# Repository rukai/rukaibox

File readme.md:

# Rukaibox

A custom hitbox controller for platform fighters.
The PCB used is the [gram slim PCB](https://gramctrl.com/products/gram-slim-pcb)
I have a fork of the PCB in this repo purely because I wanted to tweak some things for my own usage while remaining compatible with the standard gram slim PCB.

This design might be interesting to you if you want a fully 3D printable enclosure with a built in lid that flips underneath the controller when in use.
But keep in mind that when the lid is open, it exposes the PCB as an aesthetic choice, which comes with a risk of damage to the PCB.

I also personally use my own [rukaibox firmware](https://github.com/rukai/rukaibox_firmware).
But the [stock gram haybox firmware](https://github.com/GRAMCTRL/HayBox-GRAM) also works just fine and supports a wider range of protocols, games and MCUs.

## BOM

* A gram slim PCB
  * I ordered mine from jlcpcb from the designs in this repo
  * But you should probably just buy yours from <https://gramctrl.com/products/gram-slim-pcb>
* All the printed parts from [the onshape designs](https://cad.onshape.com/documents/f6e7916fda654a648d842c67/w/2435c624e0afcf5d47216714/e/d2b4fc9888a125d6f744d329?renderMode=0&uiState=6768f678e653c701cfa65dbe).
  1. Convert each part to an STL by going through the `base`, `lid`, `switch plate`, `switch plate left`, `switch plate right`, `join` and `woshua` tabs at the bottom of the page.
  For each tab, click on the tab and then right click on each part on the pane on the left and select export.
  Set the format to STL and keep the rest as default.
  2. Then slice and print each STL yourself.
* M3 Screws (all with head length 3mm, head width 5.3mm):
  * 6 X [bolt length: 13.5mm](https://www.aliexpress.com/item/32810872544.html)
* 6 X [M3 square nuts 5.45mm x 5.45mm x 1.7mm](https://www.aliexpress.com/item/1005001612157787.html)
* 21 x [kailh choc hotswap sockets](https://www.aliexpress.com/item/1005003575767699.html)
* 21 x [kailh choc V1 switches](https://www.aliexpress.com/item/1005005066585322.html) (I used whites for the start button and reds for every other button)
* 21 x [kailh choc V1 buttons](https://www.aliexpress.com/item/1005006902597750.html)

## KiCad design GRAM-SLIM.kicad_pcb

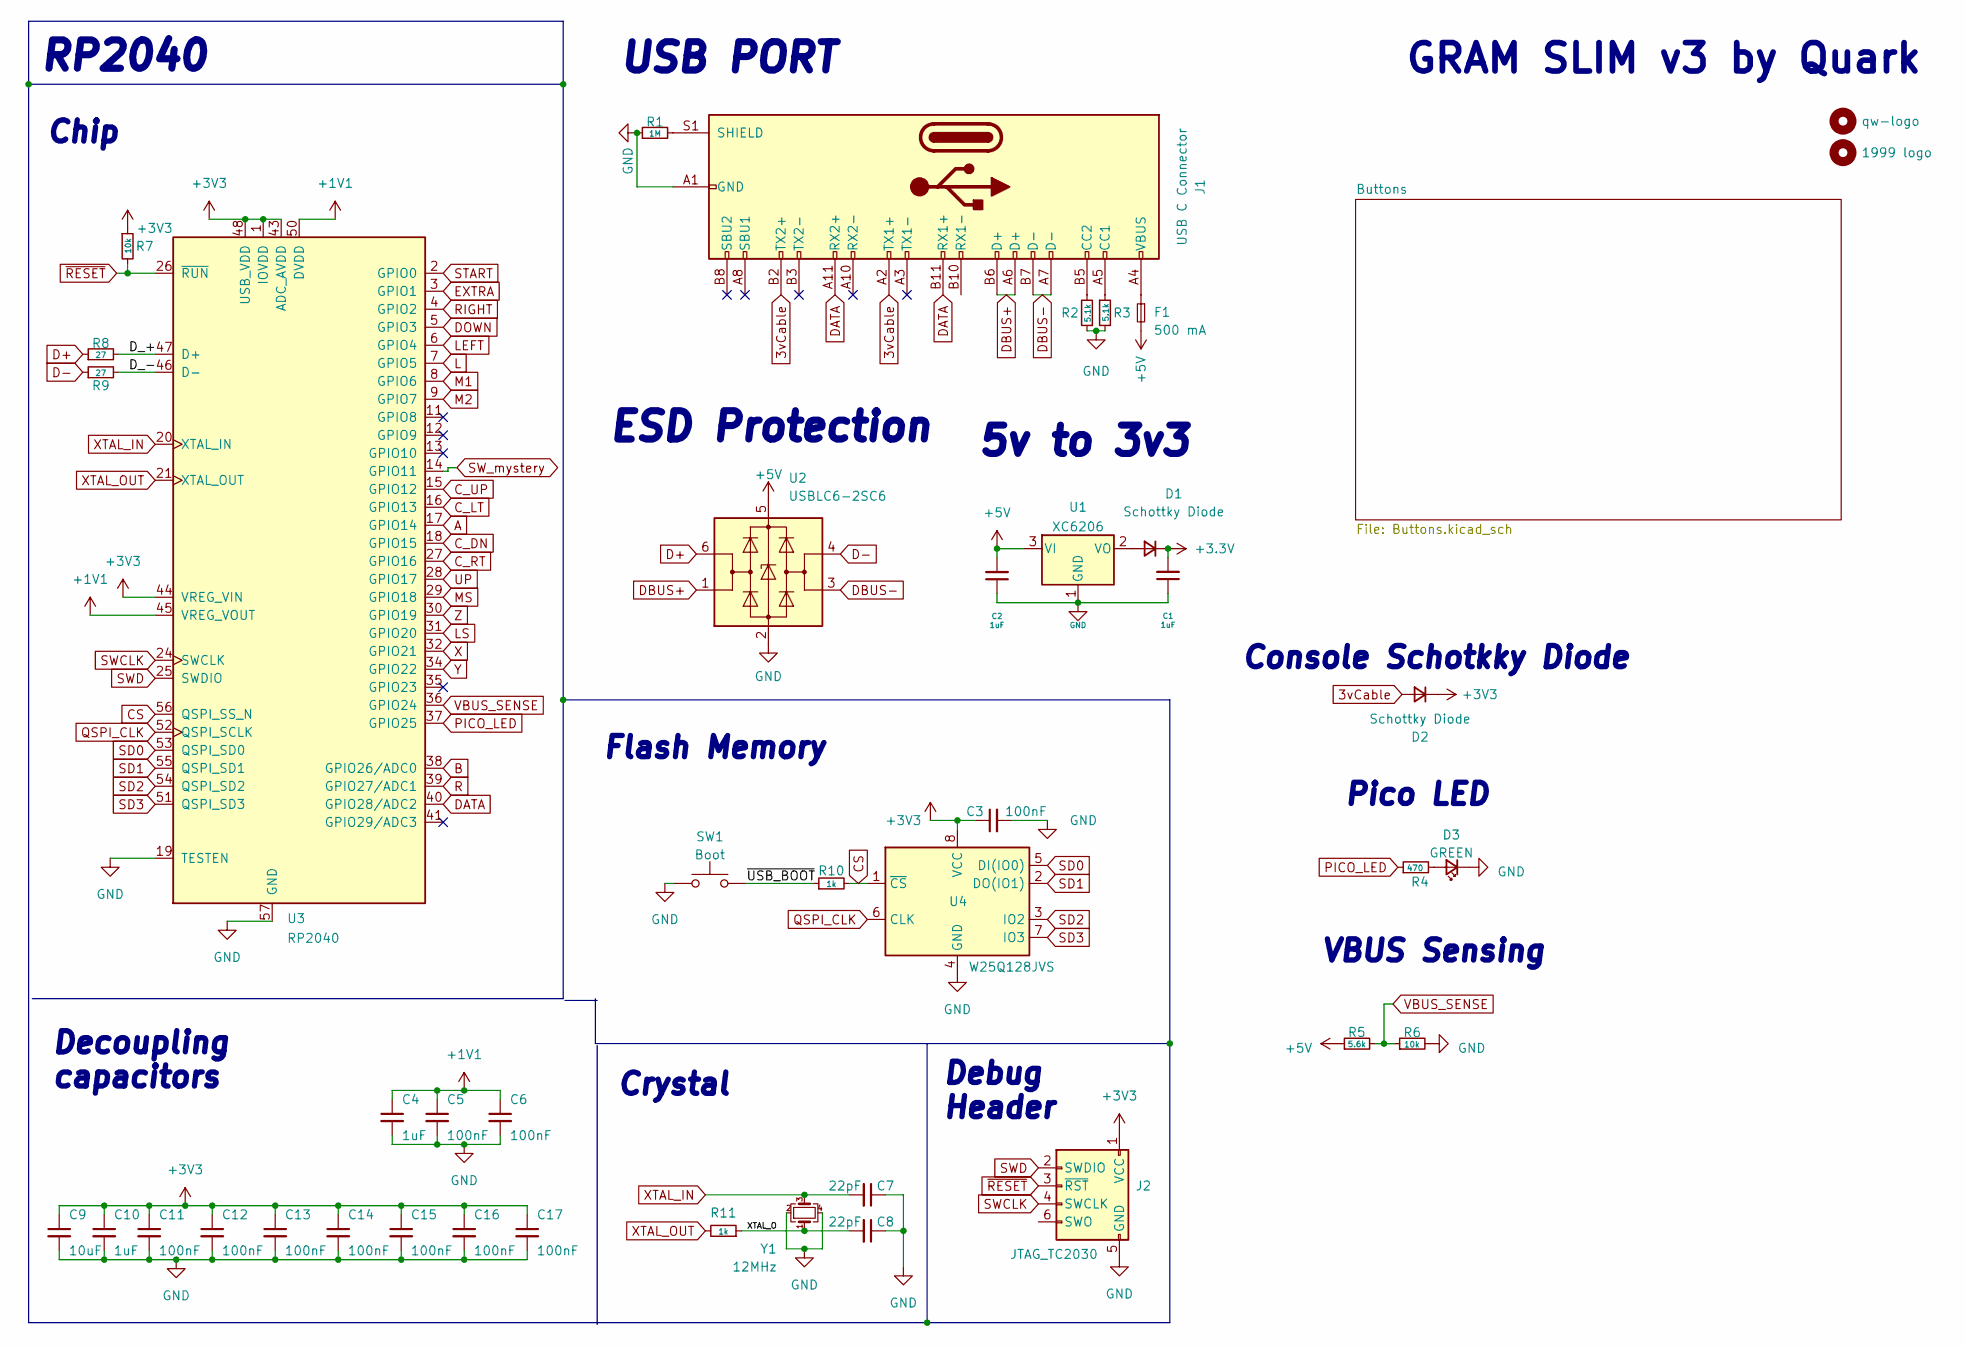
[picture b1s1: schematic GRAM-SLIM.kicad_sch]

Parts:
C1, C2, C4, C10: 1uF; C_0402_1005Metric; LCSC C52923
C3, C5, C6, C11, C12, C13, C14, C15, C16, C17: 100nF; C_0402_1005Metric; LCSC C1525
C7, C8: 22pF; C_0402_1005Metric; LCSC C1555
C9: 10uF; C_0402_1005Metric; LCSC C15525
D1, D2: Schottky Diode; D_SOD-123; LCSC C130880
D3: GREEN; LED_0805_2012Metric
F1: 500 mA; Fuse_1206_3216Metric
H1: qw-logo; qw new logo silk + copper md
H2: 1999 logo; 1999 logo md
J1: USB C Connector; TYPE-C_24P_QCHT; LCSC C456013
J2: JTAG_TC2030; CON_TC2030_outlined
R1: 1M; R_0603_1608Metric; LCSC C25190
R2, R3: 5.1k; R_0402_1005Metric; LCSC C25744
R4: 470; R_0402_1005Metric
R5: 5.6k; R_0603_1608Metric
R6: 10k; R_0603_1608Metric
R7: 10k; R_0402_1005Metric; LCSC C25744
R8, R9: 27; R_0603_1608Metric; LCSC C25190
R10, R11: 1k; R_0402_1005Metric; LCSC C11702
SW1: Boot; SW_SPST_SKQG_WithStem; LCSC C5156480
U1: XC6206; SOT-23; LCSC C5446
U2: USBLC6-2SC6; SOT-23-6
U3: RP2040; RP2040-QFN-56; LCSC C2040
U4: W25Q128JVS; SOIC-8_5.23x5.23mm_P1.27mm; LCSC C97521
Y1: 12MHz; Crystal_SMD_3225-4Pin_3.2x2.5mm; LCSC C9002

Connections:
3vCable: D2.2 (A), J1.A2 (TX1+), J1.B2 (TX2+)
+1V1: C4.1, C5.1, C6.1, U3.23 (DVDD), U3.45 (VREG_VOUT), U3.50 (DVDD)
+5V: C2.2, F1.2, R5.1, U1.3 (VI), U2.5 (VBUS)
/D_+: R8.2, U3.47 (D+)
/D_-: R9.2, U3.46 (D-)
/XTAL_O: C8.2, R11.1, Y1.1
/~USB_BOOT: R10.1, SW1.2
A: U3.17 (GPIO14); also elsewhere on the board
B: U3.38 (GPIO26/ADC0); also elsewhere on the board
CS: R10.2, U3.56 (QSPI_SS_N), U4.1 (~CS)
C_DN: U3.18 (GPIO15); also elsewhere on the board
C_LT: U3.16 (GPIO13); also elsewhere on the board
C_RT: U3.27 (GPIO16); also elsewhere on the board
C_UP: U3.15 (GPIO12); also elsewhere on the board
D+: R8.1, U2.6 (I/O1)
D-: R9.1, U2.4 (I/O2)
DATA: J1.A11 (RX2+), J1.B11 (RX1+), U3.40 (GPIO28/ADC2)
DBUS+: J1.A6 (D+), J1.B6 (D+), U2.1 (I/O1)
DBUS-: J1.A7 (D-), J1.B7 (D-), U2.3 (I/O2)
DOWN: U3.5 (GPIO3); also elsewhere on the board
EXTRA: U3.3 (GPIO1); also elsewhere on the board
GND: C1.1, C2.1, C3.2, C4.2, C5.2, C6.2, C7.1, C8.1, C9.2, C10.2, C11.2, C12.2, C13.2, C14.2, C15.2, C16.2, C17.2, D3.1 (K), J1.A1 (GND), J1.A12 (GND), J1.B1 (GND), J1.B12 (GND), J2.5 (GND), R1.1, R2.1, R3.2, R6.2, SW1.1, U1.1 (GND), U2.2 (GND), U3.19 (TESTEN), U3.57 (GND), U4.4 (GND), Y1.2, Y1.4; also elsewhere on the board
L: U3.7 (GPIO5); also elsewhere on the board
LEFT: U3.6 (GPIO4); also elsewhere on the board
LS: U3.31 (GPIO20); also elsewhere on the board
M1: U3.8 (GPIO6); also elsewhere on the board
M2: U3.9 (GPIO7); also elsewhere on the board
MS: U3.29 (GPIO18); also elsewhere on the board
unnamed: D1.2 (A), U1.2 (VO)
unnamed: D3.2 (A), R4.2
unnamed: F1.1, J1.A4 (VBUS), J1.A9 (VBUS), J1.B4 (VBUS), J1.B9 (VBUS)
unnamed: J1.A5 (CC1), R3.1
unnamed: J1.B5 (CC2), R2.2
unnamed: J1.S1 (SHIELD), R1.2
PICO_LED: R4.1, U3.37 (GPIO25)
QSPI_CLK: U3.52 (QSPI_SCLK), U4.6 (CLK)
R: U3.39 (GPIO27/ADC1); also elsewhere on the board
RIGHT: U3.4 (GPIO2); also elsewhere on the board
SD0: U3.53 (QSPI_SD0), U4.5 (DI(IO0))
SD1: U3.55 (QSPI_SD1), U4.2 (DO(IO1))
SD2: U3.54 (QSPI_SD2), U4.3 (IO2)
SD3: U3.51 (QSPI_SD3), U4.7 (IO3)
START: U3.2 (GPIO0); also elsewhere on the board
SWCLK: J2.4 (SWCLK), U3.24 (SWCLK)
SWD: J2.2 (SWDIO), U3.25 (SWDIO)
SW_mystery: U3.14 (GPIO11); also elsewhere on the board
UP: U3.28 (GPIO17); also elsewhere on the board
VBUS_SENSE: R5.2, R6.1, U3.36 (GPIO24)
X: U3.32 (GPIO21); also elsewhere on the board
XTAL_IN: C7.2, U3.20 (XTAL_IN), Y1.3
XTAL_OUT: R11.2, U3.21 (XTAL_OUT)
Y: U3.34 (GPIO22); also elsewhere on the board
Z: U3.30 (GPIO19); also elsewhere on the board
~RESET: J2.3 (~RST), R7.2, U3.26 (~RUN)

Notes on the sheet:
GRAM SLIM v3 by Quark
Flash Memory
5v to 3v3
Pico LED
Crystal
Chip
Console Schotkky Diode
RP2040
VBUS Sensing
Debug Header
USB PORT
ESD Protection
Decoupling capacitors

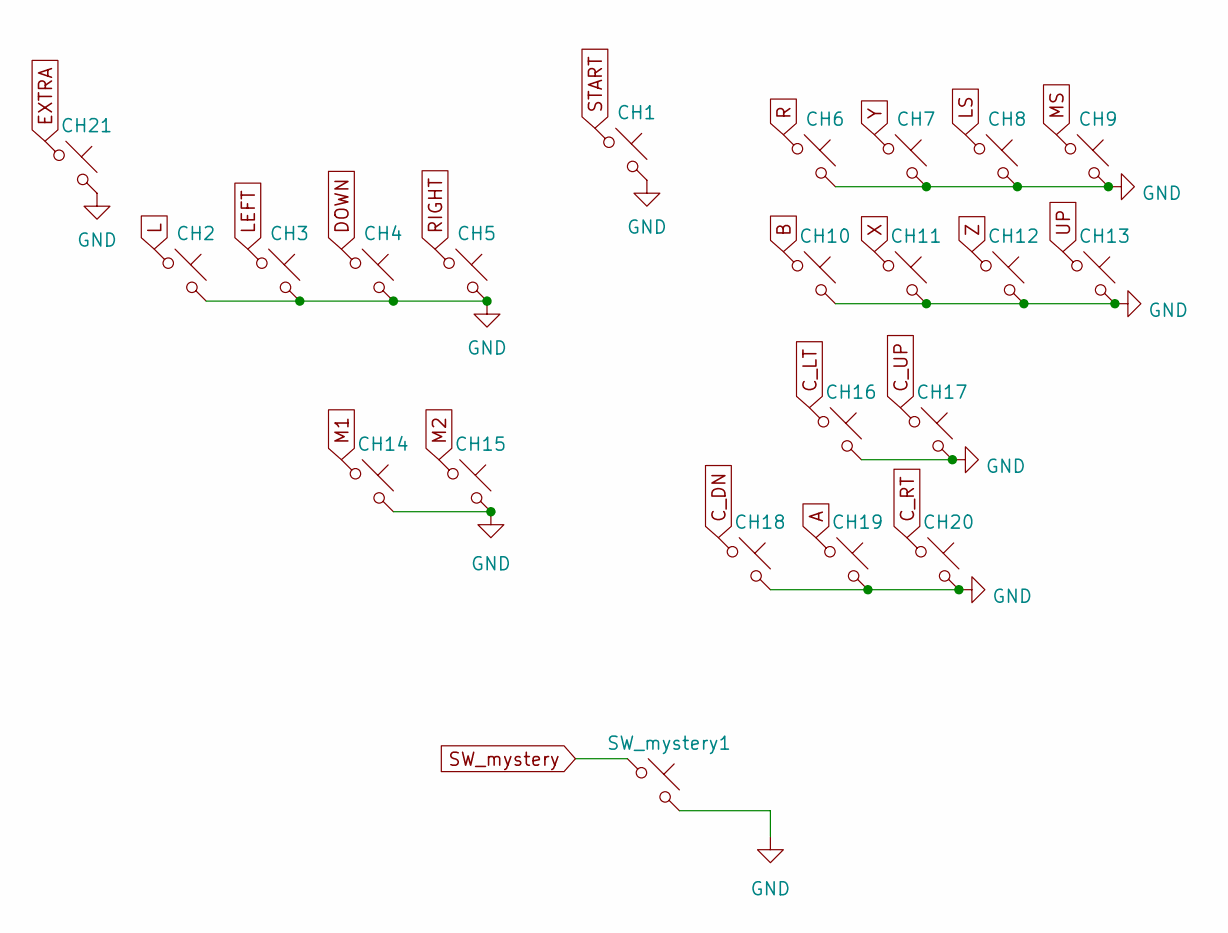
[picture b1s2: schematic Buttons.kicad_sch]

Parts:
CH1, CH2, CH3, CH4, CH5, CH6, CH7, CH8, CH9, CH10, CH11, CH12, CH13, CH14, CH15, CH16, CH17, CH18, CH19, CH20, CH21: choc_SW_HS; SW_choc_v1_HS_1u
SW_mystery1: SW_mystery??; SW_SPST_CK_RS282G05A3; JLCPCB Part # C5117870

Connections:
A: CH19.1; also elsewhere on the board
B: CH10.1; also elsewhere on the board
C_DN: CH18.1; also elsewhere on the board
C_LT: CH16.1; also elsewhere on the board
C_RT: CH20.1; also elsewhere on the board
C_UP: CH17.1; also elsewhere on the board
DOWN: CH4.1; also elsewhere on the board
EXTRA: CH21.1; also elsewhere on the board
GND: CH1.2, CH2.2, CH3.2, CH4.2, CH5.2, CH6.2, CH7.2, CH8.2, CH9.2, CH10.2, CH11.2, CH12.2, CH13.2, CH14.2, CH15.2, CH16.2, CH17.2, CH18.2, CH19.2, CH20.2, CH21.2, SW_mystery1.2; also elsewhere on the board
L: CH2.1; also elsewhere on the board
LEFT: CH3.1; also elsewhere on the board
LS: CH8.1; also elsewhere on the board
M1: CH14.1; also elsewhere on the board
M2: CH15.1; also elsewhere on the board
MS: CH9.1; also elsewhere on the board
R: CH6.1; also elsewhere on the board
RIGHT: CH5.1; also elsewhere on the board
START: CH1.1; also elsewhere on the board
SW_mystery: SW_mystery1.1; also elsewhere on the board
UP: CH13.1; also elsewhere on the board
X: CH11.1; also elsewhere on the board
Y: CH7.1; also elsewhere on the board
Z: CH12.1; also elsewhere on the board

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
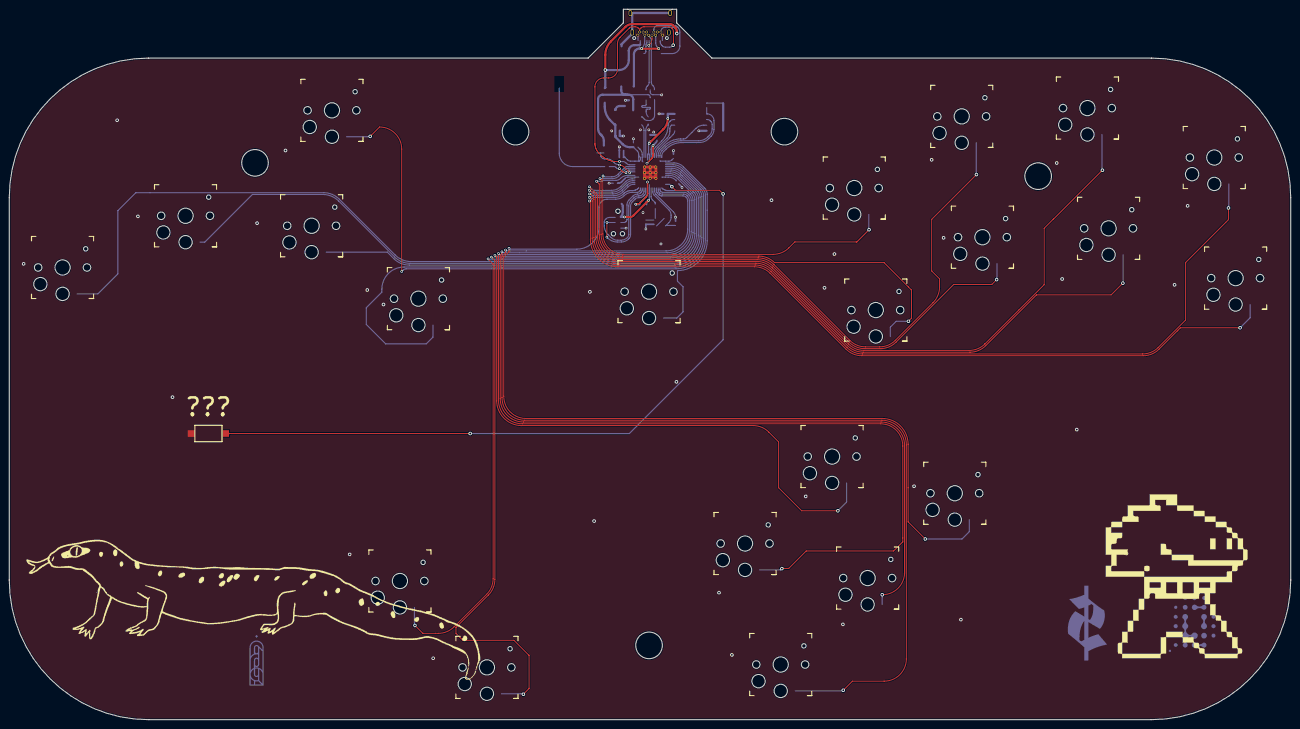
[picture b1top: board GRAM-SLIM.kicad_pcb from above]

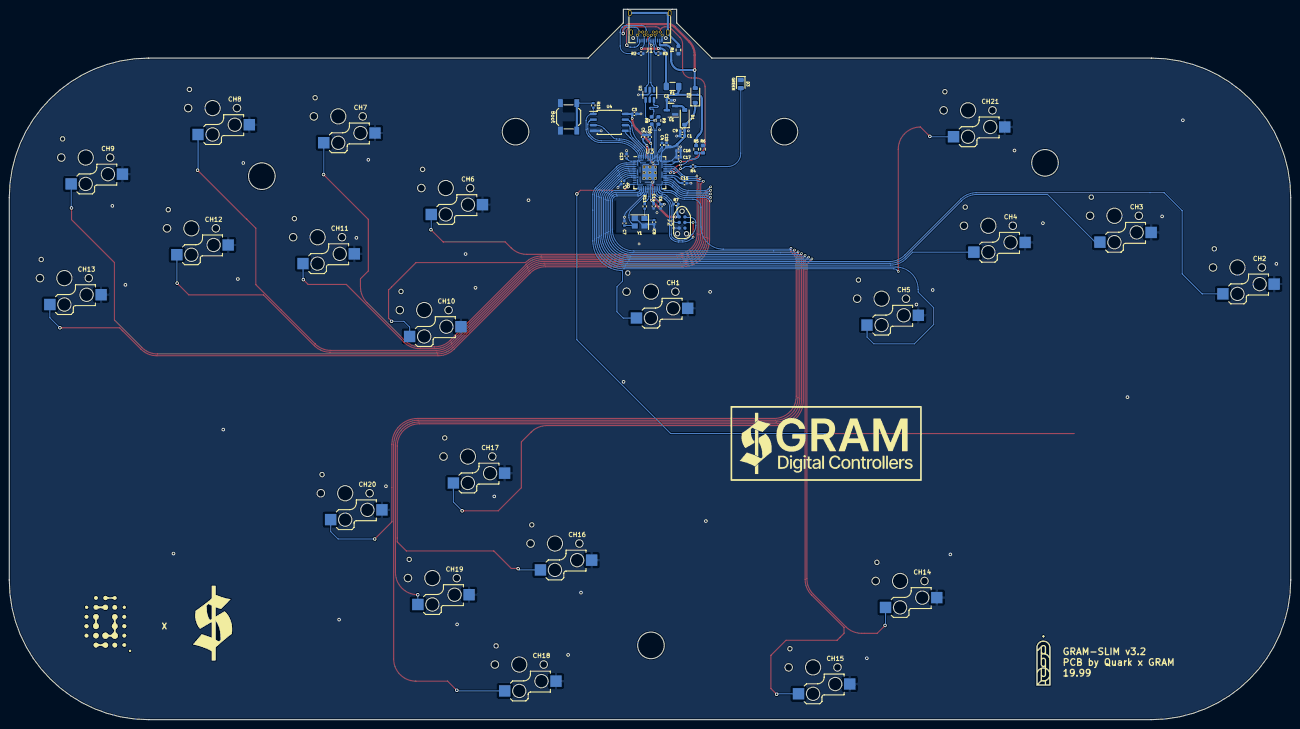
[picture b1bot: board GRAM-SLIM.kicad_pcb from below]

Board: 2 copper layers, 288.8 x 160.1 mm, 64 parts (42 on the bottom side), 55 nets.

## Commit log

2024-12-15 modifications
2024-12-23 Move pcb into sub directory and add readme
2025-02-02 Add images + improve description
